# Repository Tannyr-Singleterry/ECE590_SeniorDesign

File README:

Always before you do any work
git pull

If you need to push a change.

git add .

git status (make sure everything is green and the files you want to change are in there)

git commit -m"COMMIT MESSAGE"

git push

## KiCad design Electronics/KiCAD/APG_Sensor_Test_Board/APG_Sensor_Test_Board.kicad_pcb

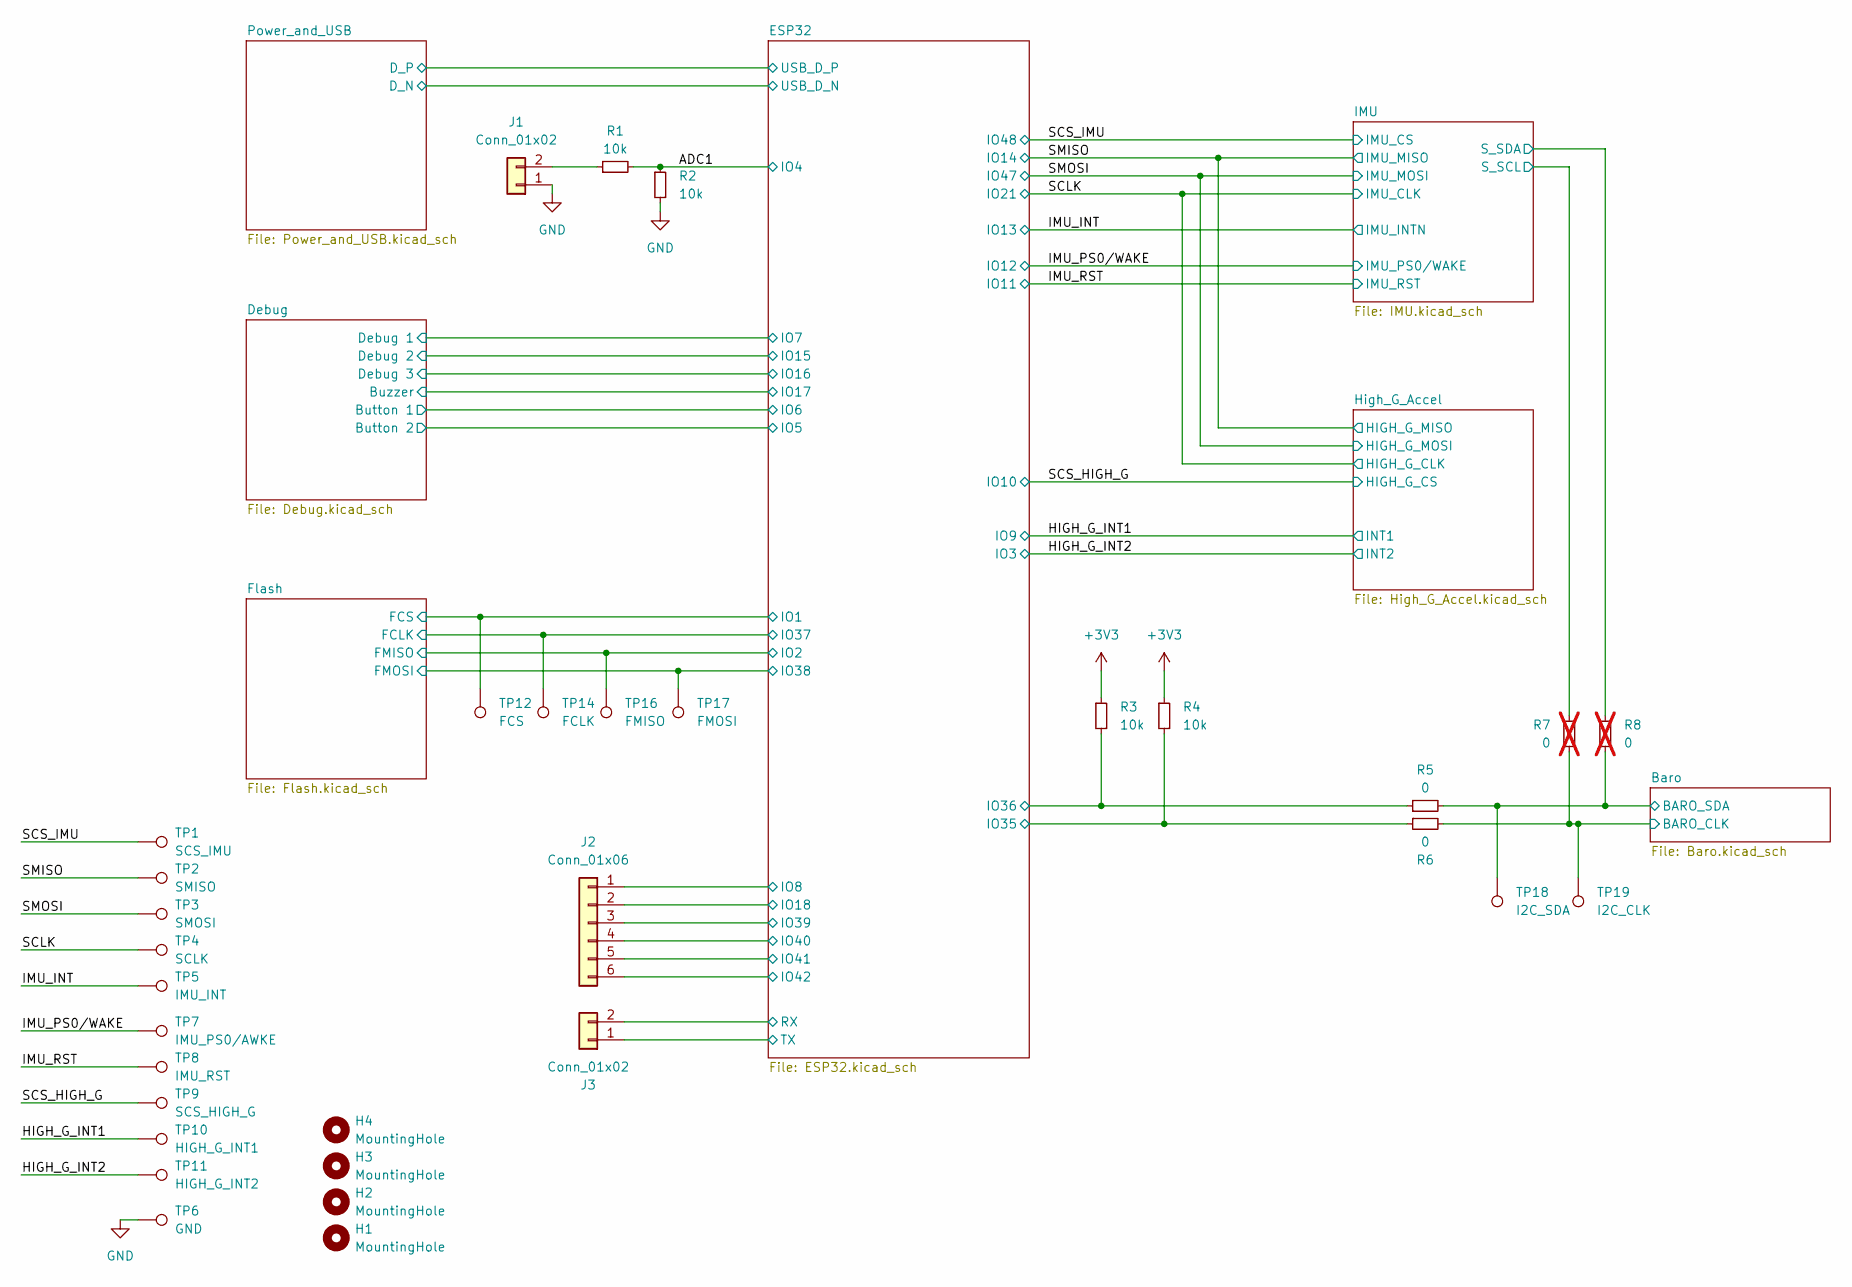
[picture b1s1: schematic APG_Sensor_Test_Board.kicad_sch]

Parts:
H1, H2, H3, H4: MountingHole; MountingHole_3.2mm_M3
J1, J3: Conn_01x02; PinHeader_1x02_P2.54mm_Vertical
J2: Conn_01x06; PinHeader_1x06_P2.54mm_Vertical
R1, R2, R3, R4: 10k; R_0603_1608Metric
R5, R6: 0; R_0603_1608Metric
R7, R8: 0; R_0603_1608Metric; not fitted
TP1: SCS_IMU; TestPoint_Pad_D1.0mm
TP2: SMISO; TestPoint_Pad_D1.0mm
TP3: SMOSI; TestPoint_Pad_D1.0mm
TP4: SCLK; TestPoint_Pad_D1.0mm
TP5: IMU_INT; TestPoint_Pad_D1.0mm
TP6: GND; TestPoint_Pad_D1.0mm
TP7: IMU_PS0/AWKE; TestPoint_Pad_D1.0mm
TP8: IMU_RST; TestPoint_Pad_D1.0mm
TP9: SCS_HIGH_G; TestPoint_Pad_D1.0mm
TP10: HIGH_G_INT1; TestPoint_Pad_D1.0mm
TP11: HIGH_G_INT2; TestPoint_Pad_D1.0mm
TP12: FCS; TestPoint_Pad_D1.0mm
TP14: FCLK; TestPoint_Pad_D1.0mm
TP16: FMISO; TestPoint_Pad_D1.0mm
TP17: FMOSI; TestPoint_Pad_D1.0mm
TP18: I2C_SDA; TestPoint_Pad_D1.0mm
TP19: I2C_CLK; TestPoint_Pad_D1.0mm

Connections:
+3V3: R3.1, R4.1; also elsewhere on the board
/ADC1: R1.2, R2.1; also elsewhere on the board
/Baro/BARO_CLK: R6.2, R7.1, TP19.1; also elsewhere on the board
/Baro/BARO_SDA: R5.2, R8.1, TP18.1; also elsewhere on the board
/ESP32/IO1: TP12.1; also elsewhere on the board
/ESP32/IO2: TP16.1; also elsewhere on the board
/ESP32/IO8: J2.1; also elsewhere on the board
/ESP32/IO18: J2.2; also elsewhere on the board
/ESP32/IO35: R4.2, R6.1; also elsewhere on the board
/ESP32/IO36: R3.2, R5.1; also elsewhere on the board
/ESP32/IO37: TP14.1; also elsewhere on the board
/ESP32/IO38: TP17.1; also elsewhere on the board
/ESP32/IO39: J2.3; also elsewhere on the board
/ESP32/IO40: J2.4; also elsewhere on the board
/ESP32/IO41: J2.5; also elsewhere on the board
/ESP32/IO42: J2.6; also elsewhere on the board
/ESP32/RX: J3.2; also elsewhere on the board
/ESP32/TX: J3.1; also elsewhere on the board
/HIGH_G_INT1: TP10.1; also elsewhere on the board
/HIGH_G_INT2: TP11.1; also elsewhere on the board
/IMU/S_SCL: R7.2; also elsewhere on the board
/IMU/S_SDA: R8.2; also elsewhere on the board
/IMU_INT: TP5.1; also elsewhere on the board
/IMU_PS0/WAKE: TP7.1; also elsewhere on the board
/IMU_RST: TP8.1; also elsewhere on the board
/SCLK: TP4.1; also elsewhere on the board
/SCS_HIGH_G: TP9.1; also elsewhere on the board
/SCS_IMU: TP1.1; also elsewhere on the board
/SMISO: TP2.1; also elsewhere on the board
/SMOSI: TP3.1; also elsewhere on the board
GND: J1.1, R2.2, TP6.1; also elsewhere on the board
unnamed: J1.2, R1.1

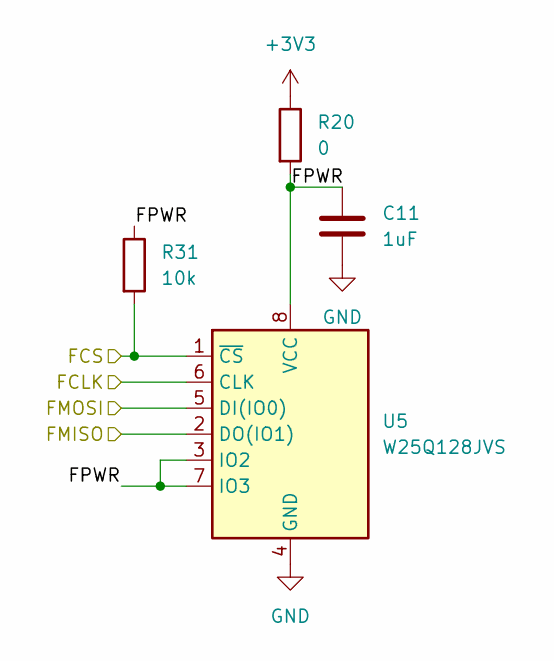
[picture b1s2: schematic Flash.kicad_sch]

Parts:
C11: 1uF; C_0603_1608Metric
R20: 0; R_0603_1608Metric
R31: 10k; R_0603_1608Metric
U5: W25Q128JVS; SOIC-8_5.23x5.23mm_P1.27mm; JLCPCB C97521

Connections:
+3V3: R20.1; also elsewhere on the board
/ESP32/IO1: R31.2, U5.1 (~CS); also elsewhere on the board
/ESP32/IO2: U5.2 (DO(IO1)); also elsewhere on the board
/ESP32/IO37: U5.6 (CLK); also elsewhere on the board
/ESP32/IO38: U5.5 (DI(IO0)); also elsewhere on the board
/Flash/FPWR: C11.1, R20.2, R31.1, U5.3 (IO2), U5.7 (IO3), U5.8 (VCC)
GND: C11.2, U5.4 (GND); also elsewhere on the board

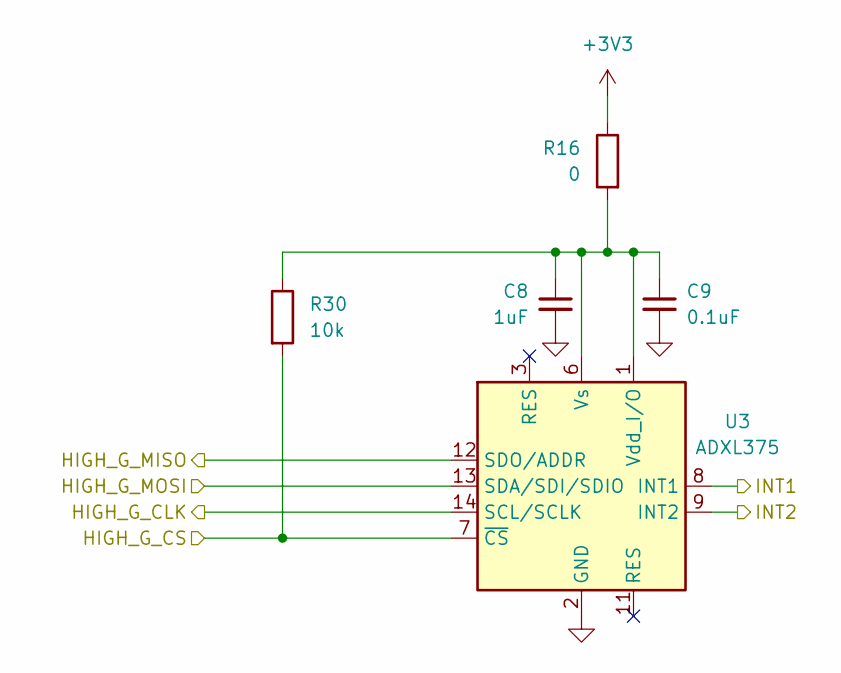
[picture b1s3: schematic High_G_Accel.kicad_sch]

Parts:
C8: 1uF; C_0603_1608Metric
C9: 0.1uF; C_0603_1608Metric
R16: 0; R_0603_1608Metric
R30: 10k; R_0603_1608Metric
U3: ADXL375; LGA-14_3x5mm_P0.8mm_LayoutBorder1x6y; JLCPCB C481898

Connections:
+3V3: R16.1; also elsewhere on the board
/HIGH_G_INT1: U3.8 (INT1); also elsewhere on the board
/HIGH_G_INT2: U3.9 (INT2); also elsewhere on the board
/SCLK: U3.14 (SCL/SCLK); also elsewhere on the board
/SCS_HIGH_G: R30.2, U3.7 (~CS); also elsewhere on the board
/SMISO: U3.12 (SDO/ADDR); also elsewhere on the board
/SMOSI: U3.13 (SDA/SDI/SDIO); also elsewhere on the board
GND: C8.2, C9.2, U3.2 (GND), U3.4 (GND), U3.5 (GND); also elsewhere on the board
unnamed: C8.1, C9.1, R16.2, R30.1, U3.1 (Vdd_I/O), U3.6 (Vs)

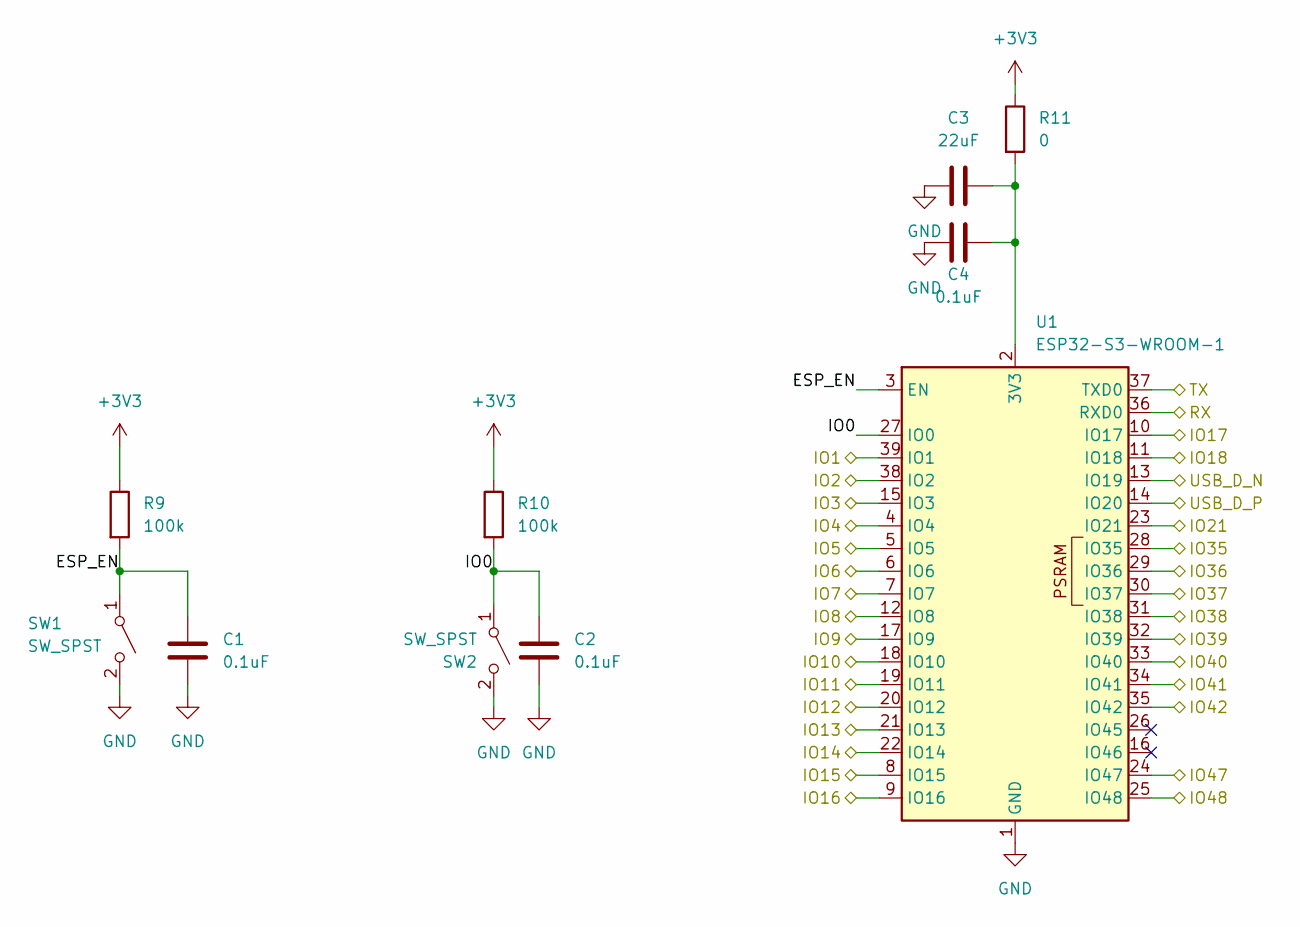
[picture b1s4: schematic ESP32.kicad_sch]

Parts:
C1, C2, C4: 0.1uF; C_0603_1608Metric
C3: 22uF; C_0603_1608Metric
R9, R10: 100k; R_0603_1608Metric
R11: 0; R_0603_1608Metric
SW1, SW2: SW_SPST; SW_PUSH_6mm_H5mm
U1: ESP32-S3-WROOM-1; JLCPCB C2913198

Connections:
+3V3: R9.1, R10.1, R11.1; also elsewhere on the board
/ADC1: U1.4 (IO4); also elsewhere on the board
/Debug/Button 1: U1.6 (IO6); also elsewhere on the board
/Debug/Button 2: U1.5 (IO5); also elsewhere on the board
/Debug/Buzzer: U1.10 (IO17); also elsewhere on the board
/Debug/Debug 1: U1.7 (IO7); also elsewhere on the board
/Debug/Debug 2: U1.8 (IO15); also elsewhere on the board
/Debug/Debug 3: U1.9 (IO16); also elsewhere on the board
/ESP32/ESP_EN: C1.1, R9.2, SW1.1 (A), U1.3 (EN)
/ESP32/IO0: C2.1, R10.2, SW2.1 (A), U1.27 (IO0)
/ESP32/IO1: U1.39 (IO1); also elsewhere on the board
/ESP32/IO2: U1.38 (IO2); also elsewhere on the board
/ESP32/IO8: U1.12 (IO8); also elsewhere on the board
/ESP32/IO18: U1.11 (IO18); also elsewhere on the board
/ESP32/IO35: U1.28 (IO35); also elsewhere on the board
/ESP32/IO36: U1.29 (IO36); also elsewhere on the board
/ESP32/IO37: U1.30 (IO37); also elsewhere on the board
/ESP32/IO38: U1.31 (IO38); also elsewhere on the board
/ESP32/IO39: U1.32 (IO39); also elsewhere on the board
/ESP32/IO40: U1.33 (IO40); also elsewhere on the board
/ESP32/IO41: U1.34 (IO41); also elsewhere on the board
/ESP32/IO42: U1.35 (IO42); also elsewhere on the board
/ESP32/RX: U1.36 (RXD0); also elsewhere on the board
/ESP32/TX: U1.37 (TXD0); also elsewhere on the board
/ESP32/USB_D_N: U1.13 (IO19); also elsewhere on the board
/ESP32/USB_D_P: U1.14 (IO20); also elsewhere on the board
/HIGH_G_INT1: U1.17 (IO9); also elsewhere on the board
/HIGH_G_INT2: U1.15 (IO3); also elsewhere on the board
/IMU_INT: U1.21 (IO13); also elsewhere on the board
/IMU_PS0/WAKE: U1.20 (IO12); also elsewhere on the board
/IMU_RST: U1.19 (IO11); also elsewhere on the board
/SCLK: U1.23 (IO21); also elsewhere on the board
/SCS_HIGH_G: U1.18 (IO10); also elsewhere on the board
/SCS_IMU: U1.25 (IO48); also elsewhere on the board
/SMISO: U1.22 (IO14); also elsewhere on the board
/SMOSI: U1.24 (IO47); also elsewhere on the board
GND: C1.2, C2.2, C3.1, C4.1, SW1.2 (B), SW2.2 (B), U1.1 (GND), U1.40 (GND), U1.41 (GND); also elsewhere on the board
unnamed: C3.2, C4.2, R11.2, U1.2 (3V3)

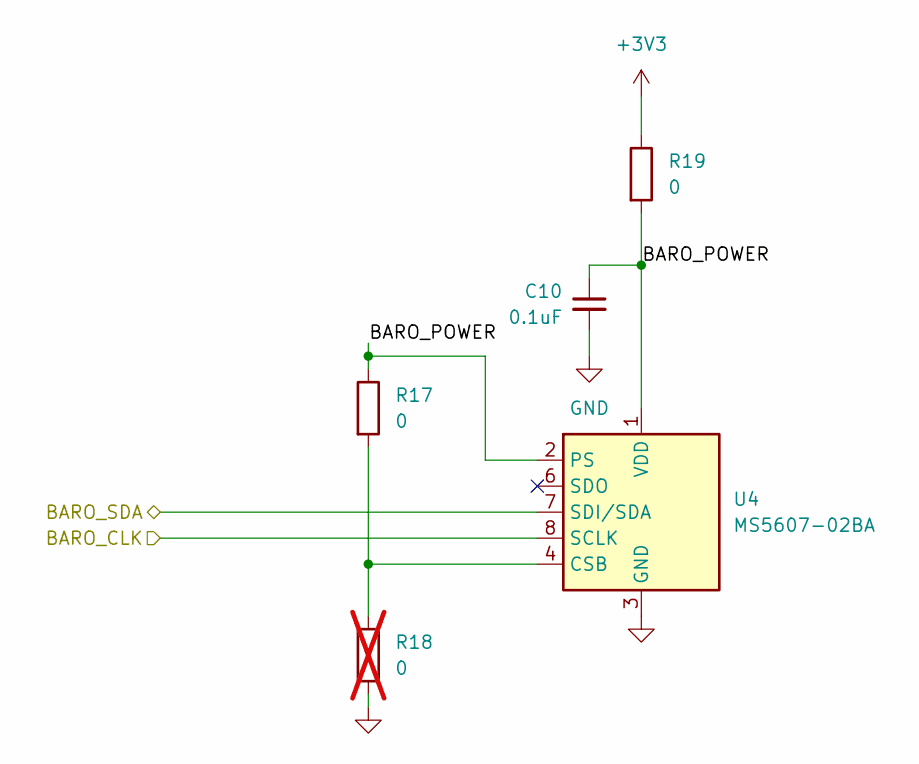
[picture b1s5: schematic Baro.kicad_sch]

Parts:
C10: 0.1uF; C_0603_1608Metric
R17, R19: 0; R_0603_1608Metric
R18: 0; R_0603_1608Metric; not fitted
U4: MS5607-02BA; LGA-8_3x5mm_P1.25mm; JLCPCB C97627

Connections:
+3V3: R19.1; also elsewhere on the board
/Baro/BARO_CLK: U4.8 (SCLK); also elsewhere on the board
/Baro/BARO_POWER: C10.1, R17.1, R19.2, U4.1 (VDD), U4.2 (PS)
/Baro/BARO_SDA: U4.7 (SDI/SDA); also elsewhere on the board
GND: C10.2, R18.2, U4.3 (GND); also elsewhere on the board
unnamed: R17.2, R18.1, U4.4 (CSB), U4.5 (CSB)

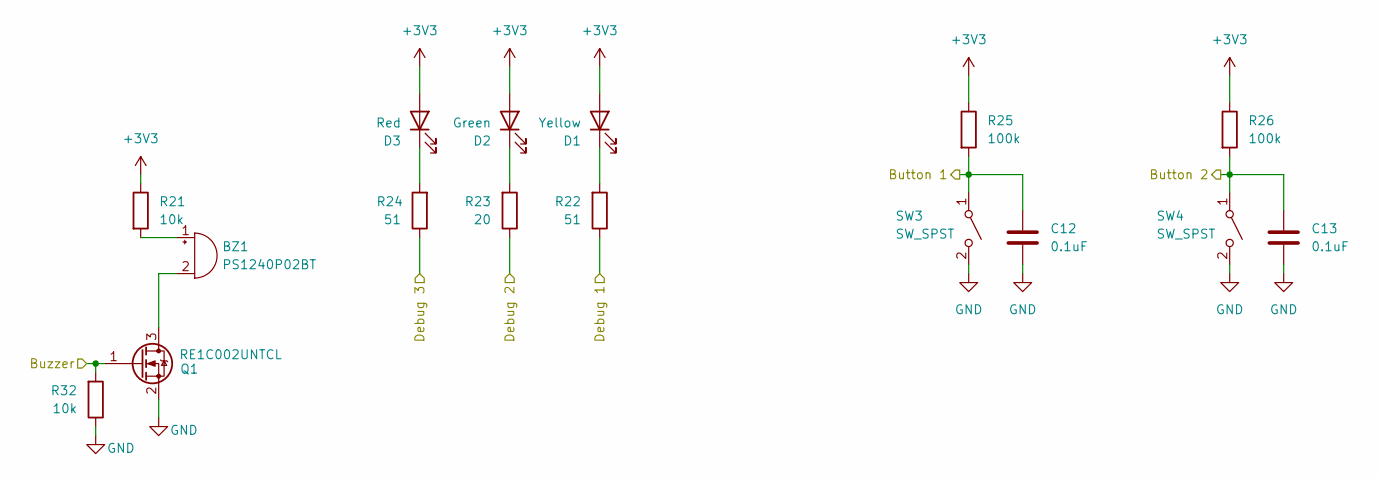
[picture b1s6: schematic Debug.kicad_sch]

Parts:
BZ1: PS1240P02BT; Buzzer_TDK_PS1240P02BT_D12.2mm_H6.5mm
C12, C13: 0.1uF; C_0603_1608Metric
D1: Yellow; LED_0805_2012Metric; JLCPCB C2296
D2: Green; LED_0805_2012Metric; JLCPCB C2297
D3: Red; LED_0805_2012Metric; JLCPCB C84256
Q1: RE1C002UNTCL; SOT-416; JLCPCB C509959
R21, R32: 10k; R_0603_1608Metric
R22, R24: 51; R_0603_1608Metric
R23: 20; R_0603_1608Metric
R25, R26: 100k; R_0603_1608Metric
SW3, SW4: SW_SPST; SW_PUSH_6mm_H5mm

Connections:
+3V3: D1.2 (A), D2.2 (A), D3.2 (A), R21.1, R25.1, R26.1; also elsewhere on the board
/Debug/Button 1: C12.1, R25.2, SW3.1 (A); also elsewhere on the board
/Debug/Button 2: C13.1, R26.2, SW4.1 (A); also elsewhere on the board
/Debug/Buzzer: Q1.1 (G), R32.2; also elsewhere on the board
/Debug/Debug 1: R22.1; also elsewhere on the board
/Debug/Debug 2: R23.1; also elsewhere on the board
/Debug/Debug 3: R24.1; also elsewhere on the board
GND: C12.2, C13.2, Q1.2 (S), R32.1, SW3.2 (B), SW4.2 (B); also elsewhere on the board
unnamed: BZ1.1 (+), R21.2
unnamed: BZ1.2 (-), Q1.3 (D)
unnamed: D1.1 (K), R22.2
unnamed: D2.1 (K), R23.2
unnamed: D3.1 (K), R24.2

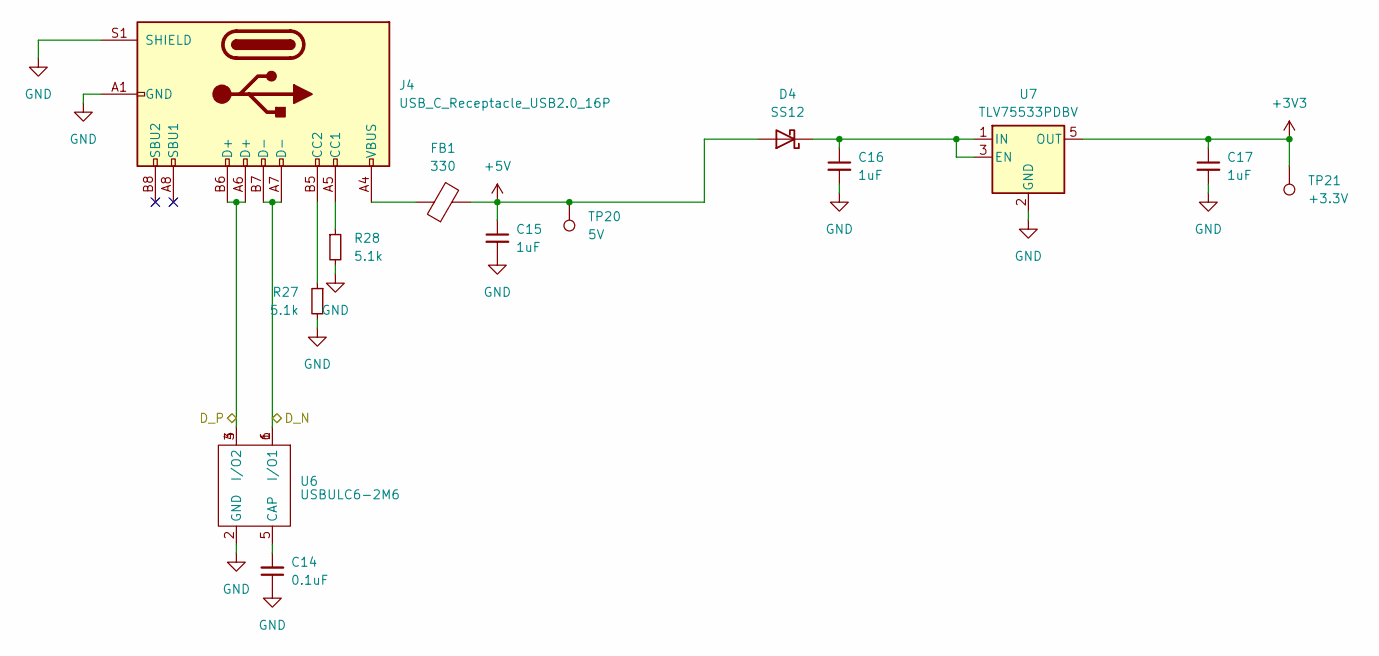
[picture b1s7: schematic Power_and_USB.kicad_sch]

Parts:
C14: 0.1uF; C_0603_1608Metric
C15, C16, C17: 1uF; C_0603_1608Metric
D4: SS12; D_SMA; JLCPCB C184027
FB1: 330; R_0805_2012Metric; JLCPCB C76819
J4: USB_C_Receptacle_USB2.0_16P; USB_C_Receptacle_GCT_USB4105-xx-A_16P_TopMnt_Horizontal; DigiKey Part # USB4105-GF-A
R27, R28: 5.1k; R_0603_1608Metric
TP20: 5V; TestPoint_Pad_D1.0mm
TP21: +3.3V; TestPoint_Pad_D1.0mm
U6: USBULC6-2M6; ST_UQFN-6L_1.5x1.7mm_P0.5mm; JLCPCB C672213
U7: TLV75533PDBV; SOT-23-5; JLCPCB C404027

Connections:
+3V3: C17.1, TP21.1, U7.5 (OUT); also elsewhere on the board
+5V: C15.1, D4.2 (A), FB1.2, TP20.1; also elsewhere on the board
/ESP32/USB_D_N: J4.A7 (D-), J4.B7 (D-), U6.1 (I/O1), U6.6 (I/O1); also elsewhere on the board
/ESP32/USB_D_P: J4.A6 (D+), J4.B6 (D+), U6.3 (I/O2), U6.4 (I/O2); also elsewhere on the board
GND: C14.1, C15.2, C16.2, C17.2, J4.A1 (GND), J4.A12 (GND), J4.B1 (GND), J4.B12 (GND), J4.S1 (SHIELD), R27.2, R28.2, U6.2 (GND), U7.2 (GND); also elsewhere on the board
unnamed: C16.1, D4.1 (K), U7.1 (IN), U7.3 (EN)
unnamed: FB1.1, J4.A4 (VBUS), J4.A9 (VBUS), J4.B4 (VBUS), J4.B9 (VBUS)
unnamed: J4.A5 (CC1), R28.1
unnamed: J4.B5 (CC2), R27.1
unnamed: C14.2, U6.5 (CAP)

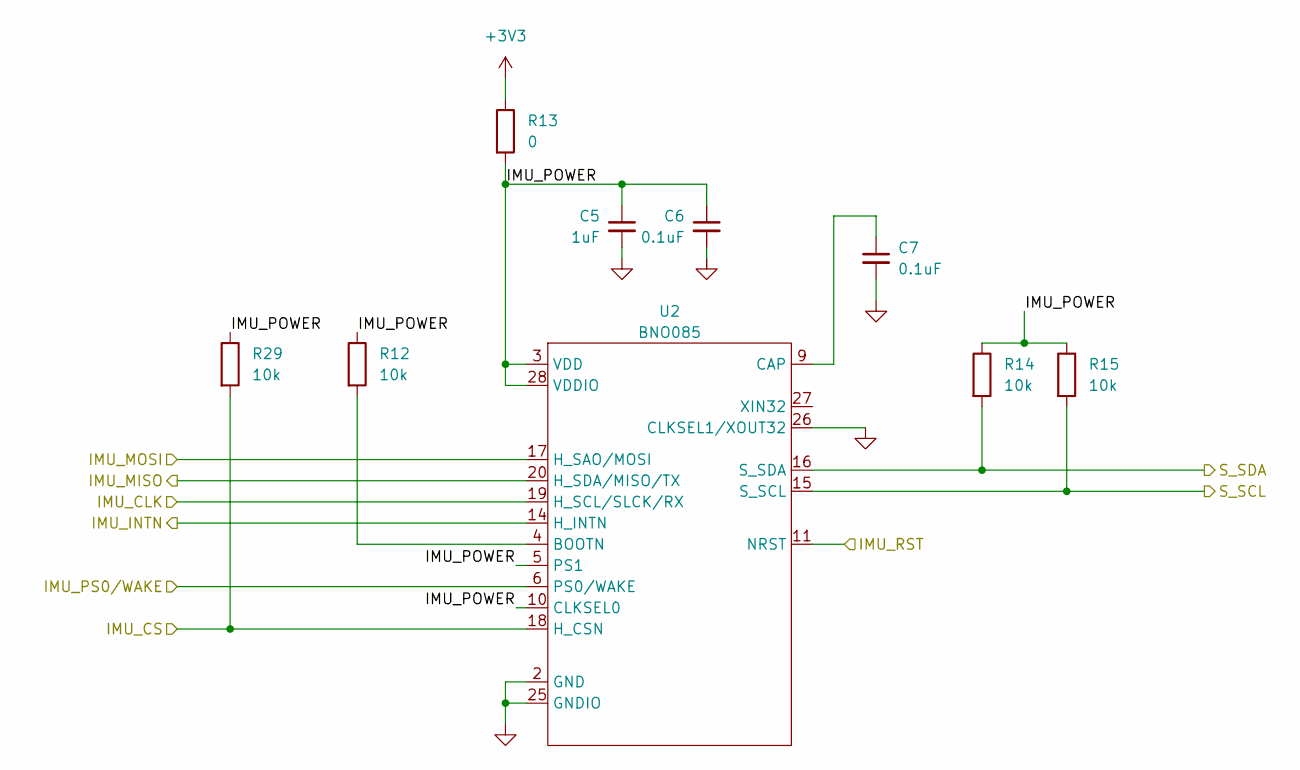
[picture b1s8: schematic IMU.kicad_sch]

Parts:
C5: 1uF; C_0603_1608Metric
C6, C7: 0.1uF; C_0603_1608Metric
R12, R14, R15, R29: 10k; R_0603_1608Metric
R13: 0; R_0603_1608Metric
U2: BNO085; LGA-28_5.2x3.8mm_P0.5mm

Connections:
+3V3: R13.1; also elsewhere on the board
/IMU/IMU_POWER: C5.1, C6.1, R12.1, R13.2, R14.1, R15.1, R29.1, U2.3 (VDD), U2.5 (PS1), U2.10 (CLKSEL0), U2.28 (VDDIO)
/IMU/S_SCL: R15.2, U2.15 (S_SCL); also elsewhere on the board
/IMU/S_SDA: R14.2, U2.16 (S_SDA); also elsewhere on the board
/IMU_INT: U2.14 (H_INTN); also elsewhere on the board
/IMU_PS0/WAKE: U2.6 (PS0/WAKE); also elsewhere on the board
/IMU_RST: U2.11 (NRST); also elsewhere on the board
/SCLK: U2.19 (H_SCL/SLCK/RX); also elsewhere on the board
/SCS_IMU: R29.2, U2.18 (H_CSN); also elsewhere on the board
/SMISO: U2.20 (H_SDA/MISO/TX); also elsewhere on the board
/SMOSI: U2.17 (H_SAO/MOSI); also elsewhere on the board
GND: C5.2, C6.2, C7.2, U2.2 (GND), U2.25 (GNDIO), U2.26 (CLKSEL1/XOUT32); also elsewhere on the board
unnamed: R12.2, U2.4 (BOOTN)
unnamed: C7.1, U2.9 (CAP)

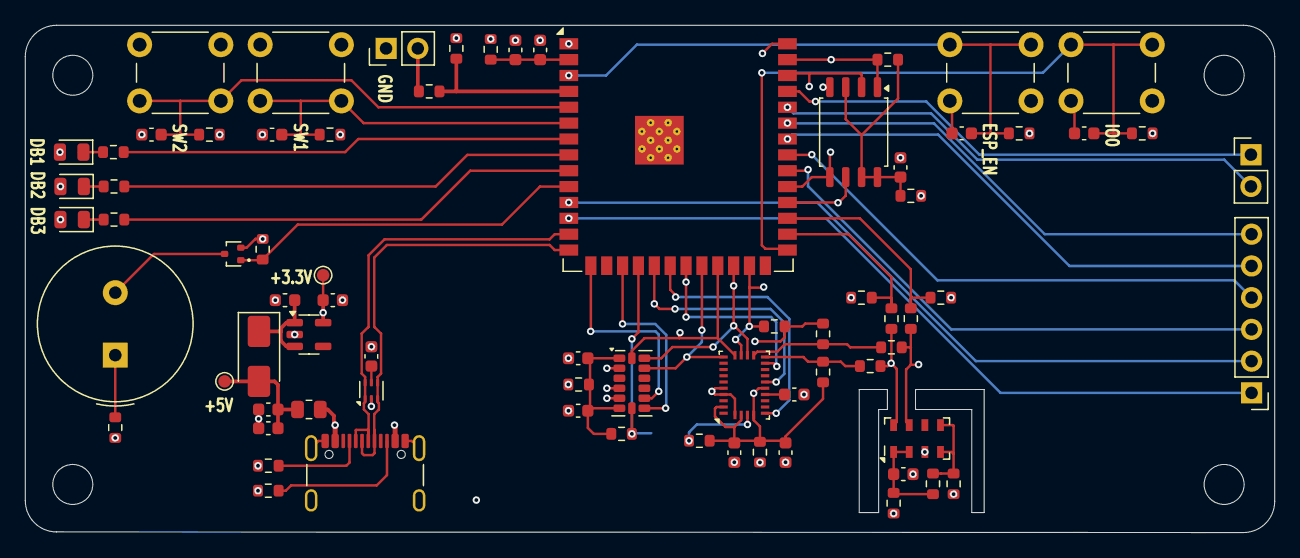
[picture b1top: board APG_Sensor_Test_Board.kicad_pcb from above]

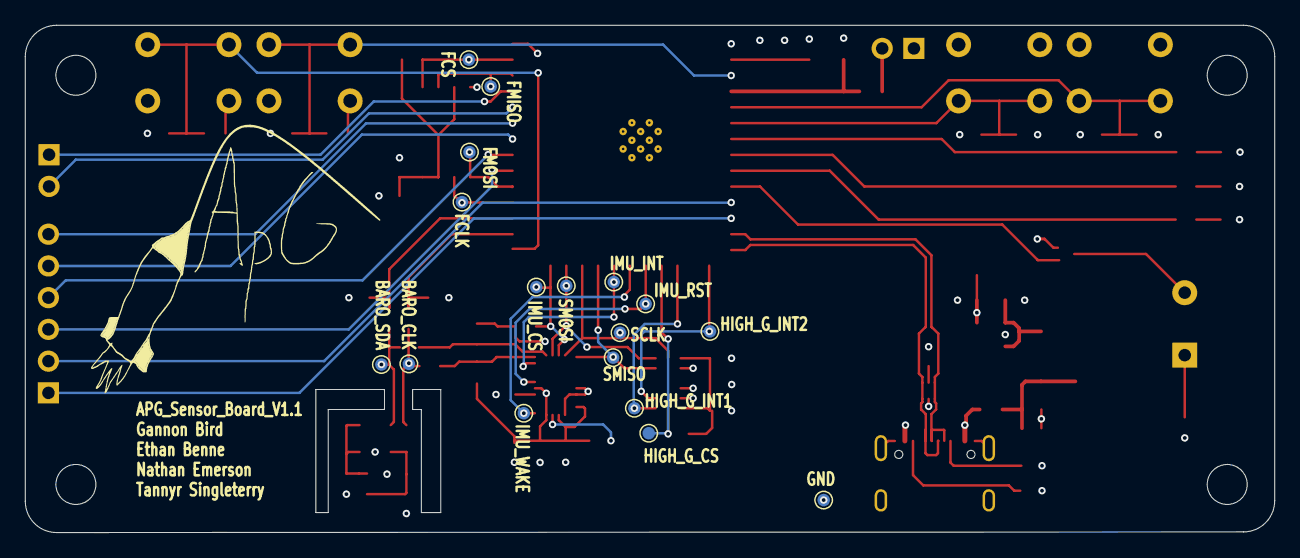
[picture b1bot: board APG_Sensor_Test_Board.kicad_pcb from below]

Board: 4 copper layers, 100.0 x 40.6 mm, 95 parts (17 on the bottom side), 61 nets.

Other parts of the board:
C14#2: 1u; C_0603_1608Metric

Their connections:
+5V: C14#2.1; also elsewhere on the board
GND: C14#2.2; also elsewhere on the board

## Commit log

2024-09-12 Added RFA in Documnets
2024-09-17 Added Brian's old senior desgin
2024-09-19 nthan test
2024-09-19 nthan remove test
2024-09-24 Added CDR folder with dox of notes
2024-09-24 Added pictures and updated CDR dox
2024-09-27 added presentation shell and empty, formatted excel sheets
2024-10-01 Created KiCAD Project for first board
2024-10-01 Created component selection Excel Sheet
2024-10-01 added some compoents to component select
2024-10-01 fixed JLC extended part Fee
2024-10-03 Pushing what i have so far
2024-10-03 final edits before meeting tomorrow
2024-10-03 added 3 things to da excel sheet
2024-10-03 CDR Tables done yay
2024-10-03 stuff i have done
2024-10-03 changed baro
2024-10-06 Presentation work
2024-10-06 presentation 99% done
2024-10-06 presentation done lmao not really
2024-10-06 stuff
2024-10-06 typo
2024-10-07 meeting edits
2024-10-07 yeet
2024-10-08 CDR presentation offically done
2024-10-09 Got started on Ocotber Draft
2024-10-11 technical section added
2024-10-11 Added more to draft. Need to add more later
2024-10-20 picked High G accelrometer
2024-10-20 Added Flash
2024-10-20 Added gantt chart
2024-10-20 kicad formating and others
2024-10-22 added week dates and auto highlighting week
2024-10-24 backups
2024-10-24 debug schematic done
2024-10-24 added flash schematic
2024-10-27 sensor schematics
2024-10-27 Cleaning up schematics
2024-10-27 Update read me
2024-10-29 10/29/24 work day
2024-10-31 Gannon inspection decision to change IMU
2024-11-01 Small schematic work
2024-11-03 TEst code maybe idk
2024-11-03 Changed IMU and changed sensors to I2C
2024-11-03 changed IMU and switched sensors to I2C
2024-11-05 Main Schematic Complete
2024-11-05 Final proposal and Gantt
2024-11-05 reaninotate and begin footprints
2024-11-07 completed footprint assignment
2024-11-07 JLC part numbers
2024-11-08 added test points
2024-11-09 MOved IMU and HIGH G to SPI other misc changes
2024-11-10 idk anymore
2024-11-10 Updated schematic a bit and added logo to pictures folder
2024-11-10 TVS protection began layout
2024-11-11 Layout and routing
2024-11-12 layout changes
2024-11-12 Made Symbol for USBULC6-2M6
2024-11-12 Worked on final presentation
2024-11-12 new tvs diode debug changes
2024-11-12 Edit PCB and Update component values
2024-11-14 APG Sensor Board V1.1 Production
2024-11-14 added coding block diagram
2024-11-14 Presentation changes ethan/gannon
2024-11-17 Worked on presentation and paper some
2024-11-24 worked on presentation and verification plan
2024-11-30 updated MCU,PCB design, and budget slides
2024-12-01 Presnetation work from meeting 12/1
2024-12-01 Small change
2024-12-02 changed standards slide
2024-12-02 Work on report
2024-12-03 Stuff that i forgot to commit eariler
2024-12-03 More report work
2024-12-03 did references hehe might delete later
2024-12-03 Presentation done
2024-12-03 Presentation final touches
2024-12-04 wahoo!
2024-12-05 report work
2024-12-05 atually made chnges
2024-12-05 Added inventory excel cause why not
2024-12-05 Forgot stuff
2024-12-05 Added the section for standards
2024-12-07 edited first few sections
2024-12-07 edited a bit more
2024-12-11 did some editing and added reference.
2024-12-11 Small report work
2024-12-12 final report schematic section
2024-12-12 Commit one
2024-12-12 Report done but appendix
2024-12-12 edit and added reference
2024-12-12 Final report done
